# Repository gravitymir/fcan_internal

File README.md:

# fcan_internal

Внутренняя шина CAN FD прибора [auto_probe](https://github.com/gravitymir/auto_probe)
и узлы на ней.

Каждый модуль прибора получает собственный микроконтроллер и выходит в общую
шину одним четырёхжильным кабелем. Мозг прибора — плата на STM32H723 — перестаёт
быть распределительным щитом на двадцать проводов и становится одним узлом среди
прочих.

## Зачем

Сейчас модули «глупые»: трансивер или усилитель без собственной логики, от
каждого к контроллеру идёт свой пучок проводов. Это работает на столе, но имеет
три недостатка, и все три упираются в одно и то же — **плату-мозг приходится
переделывать всякий раз, когда добавляется модуль.**

Шина это развязывает. Добавление шестого узла не трогает ни один из пяти
существующих и не трогает плату-мозг. Любой узел можно перевыпустить на другом
микроконтроллере через два года — и он встанет в ту же гирлянду.

Цена решения честная: узел дороже глупого модуля примерно на **$3.5**, и
прошивок становится не одна, а по одной на узел.

## Стандарт шины

Главный документ проекта — **[docs/BUS.md](docs/BUS.md)**. Там зафиксировано
всё, что обязано совпадать у всех плат: разъём, распиновка, напряжение,
топология, скорость, план идентификаторов.

Коротко:

| | |
|---|---|
| Разъём | JST PH 2.0 боковой, `S4B-PH-K-S`, **две колодки** на узел |
| Распиновка | 1 `+5V`, 2 `CANH`, 3 `CANL`, 4 `GND` |
| Питание | 5 В в кабеле, LDO 3.3 В на каждом узле |
| Топология | линейная гирлянда, терминаторы 120 Ом только на концах |
| Протокол | CAN FD с BRS, **250 кбит/с арбитраж, 1 Мбит/с данные** |
| Контроллер узла | STM32G0B1CBT6, LQFP-48 |
| Трансивер | TCAN332G |

Скорость выбрана не случайно: она совпадает со встроенным в ПЗУ загрузчиком
STM32G0B1, у которого эти параметры зашиты намертво. Благодаря этому **прошивка
любого узла заливается по той же шине**, без программатора и без собственного
загрузчика.

## Ядро узла

Всё, что одинаково на каждом узле — STM32G0B1, кварц, TCAN332G, питание
5 → 3.3 В, две колодки, USB-C, кнопки, — заморожено как схемный блок:
**[docs/CORE.md](docs/CORE.md)**, в генераторе — [`lib/gen/core.py`](lib/gen/core.py).
Новый узел — это ядро плюс своя часть. Общие скрипты сборки и проверок всех
плат лежат в [`lib/gen/`](lib/gen).

## Узлы

| Узел | Состояние | Описание |
|---|---|---|
| [volt](nodes/volt) | проектируется | вольтметр ±43 В с распознаванием типа провода |
| can | план | шлюз в CAN автомобиля, **два** трансивера |
| lin | план | два канала LIN / K-line |

`voice_cell` на шину не заходит: у ESP32 контроллер TWAI понимает только
классический CAN и в FD-шине начнёт сыпать ошибками. Он остаётся на UART и
Wi-Fi — и это правильно, потоки звука шине управления не место.

## Состояние

Проект начат 17 ноября 2026. Сейчас зафиксирован стандарт шины и ведётся
проектирование первого узла — вольтметра.

Предыдущее поколение «глупых» модулей живёт в отдельных репозиториях
([can_probe](https://github.com/gravitymir/can_probe),
[volt_probe](https://github.com/gravitymir/volt_probe),
[lin_probe](https://github.com/gravitymir/lin_probe)) и остаётся рабочим.
Их схемотехника — основа узлов здесь.

Текущая стендовая распайка глупых модулей к H723 описана в
[auto_probe/docs/WIRING.md](https://github.com/gravitymir/auto_probe/blob/master/docs/WIRING.md).

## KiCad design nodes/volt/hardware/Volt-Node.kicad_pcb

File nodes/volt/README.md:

# Узел «вольтметр»

Первый узел внутренней шины. Схема измерительного тракта взята у
[volt_probe](https://github.com/gravitymir/volt_probe) без изменений — меняется
то, что стоит **после** тракта.

Состояние: **схема готова и проверена, размещение - первый проход, разводки нет.**

| сверху | снизу |
|---|---|
|  |  |

## Что меняется против volt_probe

### Аналог больше не ходит по проводам

У `volt_probe` выход `OUT` — это **напряжение**, и оно идёт по проводу до АЦП
контроллера. Провод метровый, неэкранированный, рядом машина с зажиганием.
Это самое слабое место старого модуля: приходится следить за длиной провода и
всё равно ловить мусор.

На узле АЦП стоит **на той же плате**, в десятке миллиметров от усилителя.
По кабелю наружу уходит только дифференциальный CAN. Аналоговой проблемы больше
нет — не «уменьшена», а исчезла.

Это, пожалуй, лучший пример того, зачем вообще нужны умные узлы.

### Узел распознаёт провод сам

Тракт `volt_probe` сделан **быстрым** намеренно: полоса около 0.5 МГц, чтобы по
осциллограмме можно было опознать, что за провод под щупом — масса, питание,
LIN, K-line, CAN, ШИМ форсунок.

Раньше для этого надо было гнать поток отсчётов в мозг. По шине управления так
делать нельзя, да и незачем: у G0B1 есть АЦП на 2.5 Msps и 144 КБ ОЗУ. Узел
набирает осциллограмму локально, разбирает её сам и отдаёт на шину **вывод**, а
не поток: «постоянные 12.4 В», «K-line, 10.4 кбит/с», «ШИМ 150 Гц, 32 %».

Полную осциллограмму можно запросить отдельной командой, когда она
действительно нужна.

### Опора измеряется, а не предполагается

Опора 1.65 В получена делителем 10к/10к от того же +3.3 В, что питает АЦП, то
есть ратиометрична: ноль всегда приходится на середину шкалы. Но теперь
**вторая половина делителя доступна второму каналу АЦП** — опору можно мерить, а
не считать идеальной, и вычитать её дрейф из результата.

### Коэффициент зашит в прошивку, а не в шелкографию

`V = (V_out − 1.65) × 26.11`

На платах `volt_probe` первой партии напечатано `x27.1` — это ошибка, показания
по ней завышены на 3.8 %. Здесь число живёт в прошивке узла, и наружу идёт уже
готовое напряжение в вольтах. Ошибиться при чтении шелкографии больше негде.

## Состав платы

### Измерительный тракт — как в volt_probe

| | |
|---|---|
| LMV358 | обе половинки: дифусилитель и буфер опоры |
| R1, R2 — 470 кОм 0805 | вход, 150 В на корпус |
| R3, R4 — 18 кОм | коэффициент `18/470 = 0.0383` |
| R5, R6 — 10 кОм | делитель опоры 1.65 В |
| R7 220 Ом + C1 470 пФ | развязка от входной ёмкости АЦП |
| D1, D2 — BAT54S | клампы входов ОУ к рельсам |

Диапазон ±43 В, входное сопротивление около 488 кОм на щуп, вход держит выбросы
до ±80 В и случайные 220 В.

Щупы припаиваются проводами прямо к плате — колодки для них не ставим.

### Новое: мозг, шина, питание

Это **ядро узла** — общий для всех узлов схемный блок. Полный состав, занятые
выводы и правила — в [docs/CORE.md](../../docs/CORE.md). В генераторе этой
платы описан только измерительный тракт и то, где на плате стоит ядро.

| | |
|---|---|
| STM32G0B1CBT6 | LQFP-48, кварц обязателен |
| TCAN332G | трансивер CAN FD |
| AP2210K-3.3 | LDO из 5 В шины в 3.3 В, вход до 13.2 В, защита от переполюсовки |
| J1, J2 | `S4B-PH-K-S` — шина, параллельно, гирляндой |
| JP1 | 120 Ом терминатор на перемычке, **разомкнут** |
| J3 | USB-C — прошивка и питание на столе |
| SW1, SW2 | RESET и BOOT |

### Про стабилизатор

**AP2210K-3.3** (`C176959`), SOT-23-5 — 2.9 × 1.6 мм, около 10 ¢. Вместе с
входным 1 мкФ, выходной ёмкостью (её на `+3V3` и так 7.7 мкФ под контроллер) и
100 пФ на `BYP` это примерно 9 мм² платы. На фоне USB-C шириной 9 мм и двух
диодов SMA по 4.3 × 2.6 мм стабилизатор — не то, что занимает место.

Взят не самый дешёвый AP2112K, а AP2210K, и вот из-за чего:

| | AP2112K-3.3 (`C51118`) | **AP2210K-3.3** (`C176959`) |
|---|---|---|
| вход, рабочий / предел | 6 В / 6.5 В | **13.2 В / 15 В** |
| обратная полярность | не защищён | **защищён** |
| температура | до +85 °C | **до +125 °C** |
| подавление помехи, 100 Гц | 65 дБ | **75 дБ** |
| падение при полном токе | 250 мВ | 250 мВ |
| ток | 600 мА | 300 мА |

Ток здесь единственный пункт в пользу AP2112K, и он неважен: узел берёт около
50 мА. Зато первые три пункта важны все три. Колодка шины механически такая же,
как все остальные колодки прибора, и в машине в неё рано или поздно попадут
12 В — это должно кончаться руганью, а не заменой всех узлов сразу. Прибор
работает в машине, где +85 °C на плате летом вполне достижимы. А подавление
помехи идёт прямо в точность: опора 1.65 В ратиометрична от `+3V3`, так что
шум питания становится шумом измерения.

**Замена пин-совместимая.** Выводы 1 VIN / 2 GND / 3 EN / 5 VOUT совпадают,
отличается только вывод 4: у AP2210 это `BYP`, у AP2112K — `NC`. Поэтому если
AP2210K кончится на складе, в ту же плату ставится AP2112K, а `C15` на выводе 4
просто перестаёт что-либо делать. Ничего перерисовывать не нужно.

Остаться на 3.3 В в кабеле было бы дешевле на эти 10 ¢, но тогда все узлы сидят
на одном рале, и дёрганый сосед качает вольтметру опору. Разбор — в
[docs/BUS.md](../../docs/BUS.md).

### Про USB-C и кнопки

Прошивка идёт без программатора, потому что у G0B1 **загрузчик зашит в ПЗУ** и
умеет и USB DFU, и FDCAN. Подробности и распиновка — в
[docs/BUS.md](../../docs/BUS.md).

На столе: воткнул USB-C, зажал `BOOT`, нажал и отпустил `RESET`, отпустил
`BOOT` — плата видна как DFU-устройство. Кварц для этого не нужен, USB тактуется
от внутреннего HSI48.

В собранном приборе кнопки не нужны вовсе: узел прыгает в загрузчик по команде
с шины. Кнопки — аварийный путь, когда прошивка не стартует и команду принять
некому.

**Выводы `PD0`, `PD1`, `PA11`, `PA12`, `NRST` и `BOOT0` трогать нельзя** —
они жёстко заняты ПЗУ-загрузчиком.

## Что сделано и что нет

**Готово:** схема целиком, все номера LCSC проставлены и разрешаются.
Размещение - по сторонам света, плата 48 x 38 мм:

| | |
|---|---|
| слева по центру | USB-C `J3` окном за край, за ним CC-резисторы |
| сверху по центру | колодка шины `J1`, окном вверх |
| снизу по центру | колодка шины `J2`, окном вниз; между ней и МК - трансивер и терминатор |
| в центре | `U1`, развёрнут на 180: USB смотрит влево, АЦП и кварц вправо, CAN вниз |
| справа по центру | щупы `J4`, сразу за ними `R1`/`R2`; правый верхний угол - `U4` и остальной тракт |
| кнопки | `RESET` слева над USB, `BOOT` в правом нижнем углу |
| между USB и МК | диод `D4` и стабилизатор `U3` с конденсаторами; под USB - диод шины `D3` |
| верхний край слева | отладочная гребёнка `J5` |
| нижний край слева | колодка расширения `J6`: SPI, UART, I2C и питание (см. ниже), под `J5` по той же оси |

Перекрытий корпусов нет, замыканий нет, подписи друг на друга и на площадки не
налезают.

**Разведена** трассировщиком kroute (свой, на Rust, репозиторий `autorouter`) на двух слоях, на обоих
слоях земляной полигон. Несоединённых контактов 0, нарушений зазоров 0. Ширины
и зазоры - классы цепей в `.kicad_pro` (`lib/gen/netclass.py`): питание шины и
USB (`+5V`, `BUS5V`, `VBUS`) - 0.4 мм (держит около 1 А, вся гирлянда - около
0.4 А), `GND` и `+3V3` - 0.3 мм, CAN - 0.25, щупы - зазор 0.3 мм, остальное
0.2/0.2. Переходные отверстия 0.6/0.3. CANH/CANL и USB D+/D- идут
дифпарами - две дорожки рядом с постоянным зазором 0.25 мм (CAN - около 30 мм
вместе, USB - около 12 мм). У разъёмов шины провода пары перекрещиваются через
одну via: на `J1`/`J2` CANH и CANL стоят в обратном порядке относительно
трансивера; для CAN это безразлично.

### Колодка расширения J6

Плата, оставшаяся без дела, - готовый STM32G0B1 со стабилизатором, USB и
кнопками. Чтобы подкинуть её в другой проект, в свободный угол выведена
гребёнка 2×6 (шаг 2.54, паяется самостоятельно). Все интерфейсы аппаратные:

| Контакт | Сигнал | Вывод МК | | Контакт | Сигнал | Вывод МК |
|---|---|---|---|---|---|---|
| 1 | `3V3` | — | | 2 | `GND` | — |
| 3 | `SCK` | 42, PB3 | SPI1 | 4 | `MI` (MISO) | 43, PB4 |
| 5 | `MO` (MOSI) | 44, PB5 | SPI1 | 6 | `CS` | 41, PD3 (GPIO) |
| 7 | `TX` | 45, PB6 | USART1 | 8 | `RX` | 46, PB7 |
| 9 | `SCL` | 47, PB8 | I2C1 | 10 | `SDA` | 48, PB9 |
| 11 | `5V` | — | после диодов, ~4.7 В | 12 | `GND` | — |

Нечётные контакты - нижний ряд, у края платы; подписи на шелкографии.
`J1` и `J2` сдвинуты от центра вправо, и слева от них сверху встала `J5`,
снизу - `J6`.
Подтяжек I2C на плате нет: у готовых модулей они обычно свои. Ток с `3V3` -
сколько останется от 300 мА стабилизатора, около 200 мА.

### Проверки

Сравнивалось с `volt_probe`, по которому платы уже изготовлены, чтобы отличить
настоящие замечания от особенностей генератора:

| | Volt-Node | volt_probe (изготовлена) | |
|---|---|---|---|
| `net_conflict` | 14 | 13 | особенность связки генератор + CLI |
| `clearance` в SOT-23-8 | 6 | — (у `can_probe` те же) | зазор 0.15 мм при правиле 0.2; минимум JLCPCB 0.09 |
| `endpoint_off_grid`, `lib_symbol_mismatch` | нет | 58 и 17 | у нас чище |
| `missing_power_pin` (LMV358) | 1 | 1 | особенность символа, платы работают |
| `unconnected_items` | 0 | 0 | |
| `starved_thermal` | 2 | — | земляные выводы USB `A12`/`B1`: одна спица к полигону вместо двух, к земле они ещё и дорожкой |

ERC поймал одну настоящую ошибку: `SWDIO` висел в воздухе. Исправлено - добавлена
отладочная гребёнка `J5`.

### Что нужно поправить на следующем проходе

- **Посмотреть разводку глазами.** Трассировщик выпрямляет дорожки сам, но
  кварц и аналоговый вход стоит проверить взглядом.
- **Защиты по USB нет.** Супрессоры на `D+`/`D-` и на `VBUS` не поставлены.
- **Раздел земли** между аналоговым трактом и цифрой не продуман: выиграв на
  длине провода, можно проиграть на помехах от самого микроконтроллера.
- `JP1` даёт одно косметическое замечание DRC: у футпринта стоит флаг
  «исключить из BOM», у символа нет. На плату не влияет.

## Сборка

```bash
sh nodes/volt/hardware/gen/check.sh
```

Дорожки берутся из `hardware/Volt-Node.routes.json` - это трассы kroute
(рядом `Volt-Node.routes.png` - картинка разводки). После перестановки деталей
они к плате уже не подходят, разводку надо сделать заново:

```bash
cd nodes/volt/hardware
python gen/build.py . && python ../../../lib/gen/route.py Volt-Node.kicad_pcb
sh gen/check.sh
```

`route.py` берёт `kroute` из переменной `KROUTE`, из `PATH` или из соседнего
репозитория `../autorouter/target/release/`. Дифпары и прочие правила
трассировки - `lib/gen/kroute.toml` (узел может положить свой `kroute.toml`
рядом с платой).

Нужен Python из KiCad 10. Скрипт пересобирает плату, прогоняет DRC со сверкой
схемы, ERC и собственные проверки, и заново выписывает `BOM.csv` и `PINOUT.csv` -
из той платы, которая только что собрана, чтобы спецификация не отставала от
схемы молча.

### Библиотеки рядом с платой

Проект не полагается на то, что у открывающего установлены нужные библиотеки
KiCad. Рядом с платой лежат свои:

- `fcan.pretty` + `fp-lib-table` - футпринты, скопированные из системных;
- `fcan.kicad_sym` + `sym-lib-table` - символы, которых в KiCad нет.

Сейчас такой символ один - **AP2210K-3.3**. Он не нарисован руками:
[`lib/gen/symlib.py`](../../lib/gen/symlib.py) берёт готовый `AP2204K-1.5` (тот же
SOT-23-5, та же раскладка выводов 1/2/3/5) и правит у него только то, чем части
отличаются - вывод 4, который у AP2204K называется `NC` и имеет тип
«не подключён», а у AP2210K это `BYP` с конденсатором. Так символ по виду и по
сетке совпадает с остальными, а в правке видна ровно суть различия - и имя
символа не врёт про то, какая это микросхема.

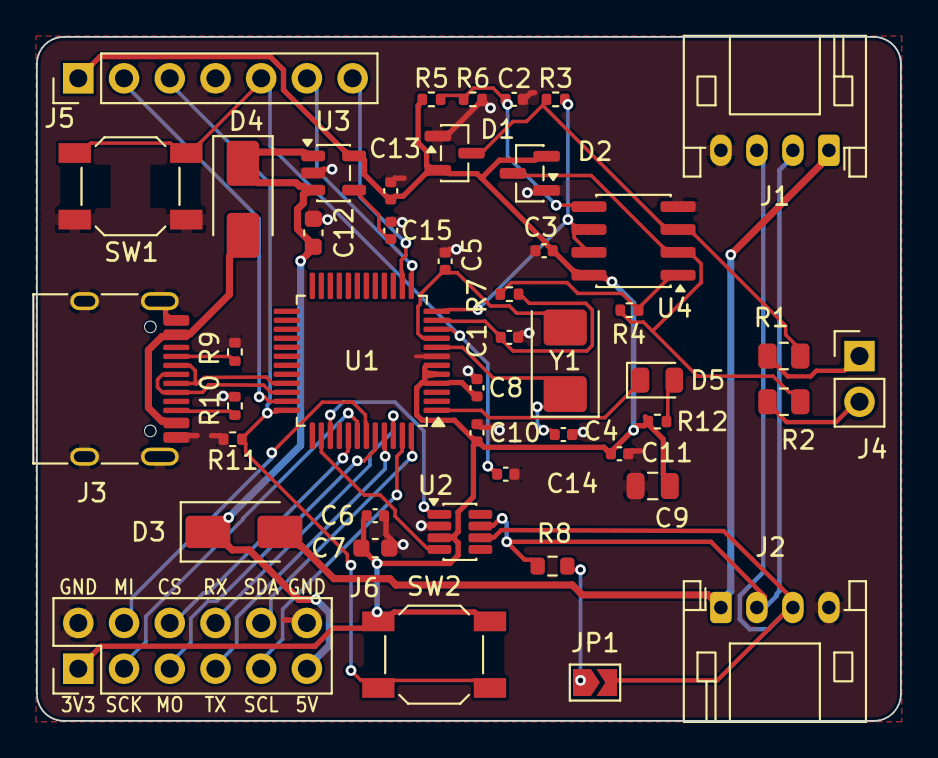
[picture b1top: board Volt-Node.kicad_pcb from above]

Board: 2 copper layers, 48.0 x 38.0 mm, 46 parts (0 on the bottom side), 40 nets.

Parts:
C1: 470pF; C_0402_1005Metric
C2, C3, C6, C8, C10, C14: 100nF; C_0402_1005Metric
C4, C5: 33pF; C_0402_1005Metric
C7, C12: 1uF; C_0603_1608Metric
C9: 4.7uF; C_0805_2012Metric
C11, C13: 1uF; C_0402_1005Metric
C15: 100pF; C_0402_1005Metric
D1, D2: BAT54S; SOT-23
D3, D4: SS34; D_SMA
D5: LED; LED_0805_2012Metric
J1, J2: BUS; JST_PH_S4B-PH-K_1x04_P2.00mm_Horizontal
J3: USB-C; USB_C_Receptacle_HRO_TYPE-C-31-M-12
J4: PROBE; PinHeader_1x02_P2.54mm_Vertical
J5: DEBUG; PinHeader_1x07_P2.54mm_Vertical
J6: EXP; PinHeader_2x06_P2.54mm_Vertical
JP1: TERM; SolderJumper-2_P1.3mm_Open_TrianglePad1.0x1.5mm
R1, R2: 470k; R_0805_2012Metric
R3, R4: 18k; R_0402_1005Metric
R5, R6, R11: 10k; R_0402_1005Metric
R7: 220R; R_0402_1005Metric
R8: 120R; R_0603_1608Metric
R9, R10: 5.1k; R_0402_1005Metric
R12: 1k; R_0402_1005Metric
SW1: RESET; SW_SPST_SKQG_WithoutStem
SW2: BOOT; SW_SPST_SKQG_WithoutStem
U1: STM32G0B1CBT6; LQFP-48_7x7mm_P0.5mm
U2: TCAN332G; SOT-23-8
U3: AP2210K-3.3; SOT-23-5
U4: LMV358; SOIC-8_3.9x4.9mm_P1.27mm
Y1: 8MHz; Crystal_SMD_5032-2Pin_5.0x3.2mm

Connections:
+3V3: C3.1, C6.1, C7.1, C8.1, C9.1, C10.1, C11.1, C13.1, D1.2, D2.2, J5.1, J6.1, R5.1, R12.1, SW2.2, U1.4, U1.5, U1.6, U2.3, U3.5, U4.8
+5V: C12.1, D3.1, D4.1, J6.11, U3.1, U3.3
AOUT: R4.2, R7.1, U4.1
BUS5V: D3.2, J1.1, J2.1
BYP: C15.1, U3.4
CANH: J1.2, J2.2, R8.1, U2.7
CANL: J1.3, J2.3, JP1.2, U2.6
CAN_RX: U1.38, U2.4
CAN_TX: U1.39, U2.1
CC1: J3.A5, R9.1
CC2: J3.B5, R10.1
EXP_CS: J6.6, U1.41
EXP_MISO: J6.4, U1.43
EXP_MOSI: J6.5, U1.44
EXP_RX: J6.8, U1.46
EXP_SCK: J6.3, U1.42
EXP_SCL: J6.9, U1.47
EXP_SDA: J6.10, U1.48
EXP_TX: J6.7, U1.45
FB: D2.3, R2.2, R4.1, U4.2
GND: C1.2, C2.2, C3.2, C4.2, C5.2, C6.2, C7.2, C8.2, C9.2, C10.2, C11.2, C12.2, C13.2, C14.2, C15.2, D1.1, D2.1, J1.4, J2.4, J3.A1, J3.A12, J3.B1, J3.B12, J3.SH, J5.4, J6.2, J6.12, R6.2, R9.2, R10.2, R11.2, SW1.2, U1.7, U2.2, U3.2, U4.4
INP: D1.3, R1.2, R3.1, U4.3
LED_A: D5.2, R12.2
LED_K: D5.1, U1.1
NRST: C14.1, J5.5, SW1.1, U1.10
OSC_IN: C4.1, U1.8, Y1.1
OSC_OUT: C5.1, U1.9, Y1.2
SWCLK: J5.3, R11.1, SW2.1, U1.36
SWDIO: J5.2, U1.35
TERM: JP1.1, R8.2
UART_RX: J5.7, U1.14
UART_TX: J5.6, U1.13
USB_DM: J3.A7, J3.B7, U1.33
USB_DP: J3.A6, J3.B6, U1.34
VBUS: D4.2, J3.A4, J3.A9, J3.B4, J3.B9
VIN+: J4.1, R1.1
VIN-: J4.2, R2.1
VOUT: C1.1, R7.2, U1.11
VREF: R3.2, U1.12, U4.6, U4.7
VREFD: C2.1, R5.2, R6.1, U4.5

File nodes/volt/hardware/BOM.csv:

Comment,Designator,Footprint,LCSC Part #,Qty,Note
100nF,"C10,C14,C2,C3,C6,C8",fcan:C_0402_1005Metric,C1525,6,проверить наличие на складе
100pF,C15,fcan:C_0402_1005Metric,C1546,1,проверить наличие на складе
33pF,"C4,C5",fcan:C_0402_1005Metric,C1562,2,проверить наличие на складе
1uF,"C11,C13",fcan:C_0402_1005Metric,C52923,2,проверить наличие на складе
470pF,C1,fcan:C_0402_1005Metric,C75274,1,проверить наличие на складе
1uF,"C12,C7",fcan:C_0603_1608Metric,C15849,2,проверить наличие на складе
4.7uF,C9,fcan:C_0805_2012Metric,C1779,1,проверить наличие на складе
8MHz,Y1,fcan:Crystal_SMD_5032-2Pin_5.0x3.2mm,C115962,1,проверить наличие на складе; обвязка 33 пФ - только под CL 20 пФ
SS34,"D3,D4",fcan:D_SMA,C8678,2,проверить наличие на складе
BUS,"J1,J2",fcan:JST_PH_S4B-PH-K_1x04_P2.00mm_Horizontal,C157926,2,проверить наличие на складе
LED,D5,fcan:LED_0805_2012Metric,C84256,1,проверить наличие на складе
STM32G0B1CBT6,U1,fcan:LQFP-48_7x7mm_P0.5mm,C2847904,1,проверить наличие на складе
PROBE,J4,fcan:PinHeader_1x02_P2.54mm_Vertical,,1,"гребёнка: номер не проставлен намеренно, паяется самостоятельно; нужна впаянной - впишите номер LCSC и заказывайте Standard"
DEBUG,J5,fcan:PinHeader_1x07_P2.54mm_Vertical,,1,"гребёнка: номер не проставлен намеренно, паяется самостоятельно; нужна впаянной - впишите номер LCSC и заказывайте Standard"
EXP,J6,fcan:PinHeader_2x06_P2.54mm_Vertical,,1,"гребёнка: номер не проставлен намеренно, паяется самостоятельно; нужна впаянной - впишите номер LCSC и заказывайте Standard"
1k,R12,fcan:R_0402_1005Metric,C11702,1,проверить наличие на складе
220R,R7,fcan:R_0402_1005Metric,C25091,1,проверить наличие на складе
10k,"R11,R5,R6",fcan:R_0402_1005Metric,C25744,3,проверить наличие на складе
18k,"R3,R4",fcan:R_0402_1005Metric,C25762,2,проверить наличие на складе
5.1k,"R10,R9",fcan:R_0402_1005Metric,C25905,2,проверить наличие на складе
120R,R8,fcan:R_0603_1608Metric,C22787,1,проверить наличие на складе
470k,"R1,R2",fcan:R_0805_2012Metric,C17709,2,проверить наличие на складе
LMV358,U4,fcan:SOIC-8_3.9x4.9mm_P1.27mm,C7980,1,проверить наличие на складе
BAT54S,"D1,D2",fcan:SOT-23,C47546,2,проверить наличие на складе
AP2210K-3.3,U3,fcan:SOT-23-5,C176959,1,"проверить наличие на складе; вход до 13.2 В (предел 15 В), защита от обратной полярности, -40...+125 C; пин-совместимая замена AP2112K-3.3 (C51118) - но вход только 6 В и вывод 4 у неё NC"
TCAN332G,U2,fcan:SOT-23-8,C2671083,1,проверить наличие на складе
BOOT/RESET,"SW1,SW2",fcan:SW_SPST_SKQG_WithoutStem,C318884,2,проверить наличие на складе
USB-C,J3,fcan:USB_C_Receptacle_HRO_TYPE-C-31-M-12,C165948,1,проверить наличие на складе

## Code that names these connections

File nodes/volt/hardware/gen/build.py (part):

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d = kigen.Design(NAME, "Volt-Node: вольтметр +-43 В, узел внутренней шины CAN FD")
d.prepare()

core.add(d, mcu={"11": "VOUT",     # PA0 - АЦП: измерение
                 "12": "VREF",     # PA1 - АЦП: контроль опоры 1.65 В
                 # колодка расширения J6
                 "41": "EXP_CS",   # PD3 - GPIO
                 "42": "EXP_SCK",  # PB3 - SPI1_SCK
                 "43": "EXP_MISO", # PB4 - SPI1_MISO
                 "44": "EXP_MOSI", # PB5 - SPI1_MOSI
                 "45": "EXP_TX",   # PB6 - USART1_TX
                 "46": "EXP_RX",   # PB7 - USART1_RX
                 "47": "EXP_SCL",  # PB8 - I2C1_SCL
                 "48": "EXP_SDA"}) # PB9 - I2C1_SDA

# --- измерительный тракт: как в volt_probe, один в один
P = lambda ref, lib, val, fp, nets, at: d.add(kigen.Part(ref, lib, val, "%s:%s" % fp, nets, at=at))
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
